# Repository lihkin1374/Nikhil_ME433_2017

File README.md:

Nikhil Marri
==============
March 28, 2017
----------------

My repository for ME 433: Advanced Mechatronics.

Spring quarter

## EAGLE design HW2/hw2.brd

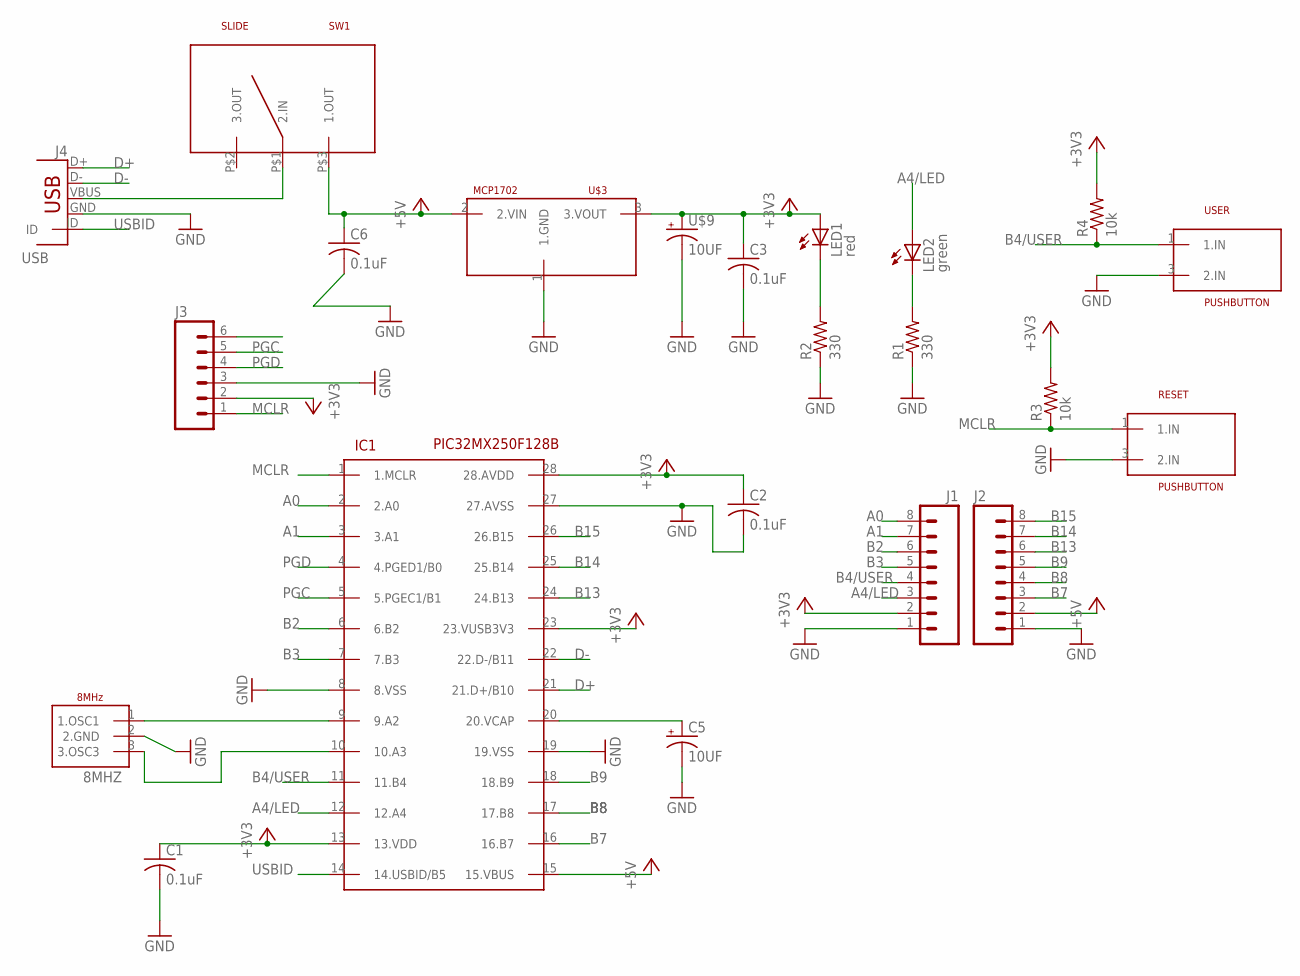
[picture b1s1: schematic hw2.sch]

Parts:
C1, C2, C3, C6: 0.1uF; C025-025X050
C5: 10UF; TT2D4
J1, J2: M08; 1X08_ROUND
J3: M06SILK_FEMALE_PTH; 1X06
J4: USB; USB-MB-H
LED1: red; LED3MM
LED2: green; LED3MM
PIC: PIC32MX250F128B; DIL28-3
R1, R2: 330; 0207/10
R3, R4: 10k; 0207/10
RESET: PUSHBUTTON; 1X03
SLIDE: SW1; SLIDEWITCH
U$2: 8MHZ; 1X03
U$3: MCP1702; TO92
U$9: 10UF; TT2D4
USER: PUSHBUTTON; 1X03

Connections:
+3V3: C1.1, C2.1, C3.1, J1.2, J3.2, LED1.A, PIC.13 (13.VDD), PIC.23 (23.VUSB3V3), PIC.28 (28.AVDD), R3.2, R4.2, U$3.3 (3.VOUT), U$9.+
+5V: C6.1, J2.2, PIC.15 (15.VBUS), SLIDE.P$3 (1.OUT), U$3.2 (2.VIN)
A0: J1.8, PIC.2 (2.A0)
A1: J1.7, PIC.3 (3.A1)
A4/LED: J1.3, LED2.A, PIC.12 (12.A4)
B2: J1.6, PIC.6 (6.B2)
B3: J1.5, PIC.7 (7.B3)
B4/USER: J1.4, PIC.11 (11.B4), R4.1, USER.1 (1.IN)
B7: J2.3, PIC.16 (16.B7)
B8: J2.4, PIC.17 (17.B8)
B9: J2.5, PIC.18 (18.B9)
B13: J2.6, PIC.24 (24.B13)
B14: J2.7, PIC.25 (25.B14)
B15: J2.8, PIC.26 (26.B15)
D+: J4.D+, PIC.21 (21.D+/B10)
D-: J4.D-, PIC.22 (22.D-/B11)
GND: C1.2, C2.2, C3.2, C5.-, C6.2, J1.1, J2.1, J3.3, J4.GND, PIC.8 (8.VSS), PIC.19 (19.VSS), PIC.27 (27.AVSS), R1.1, R2.1, RESET.3 (2.IN), U$2.2 (2.GND), U$3.1 (1.GND), U$9.-, USER.3 (2.IN)
MCLR: J3.1, PIC.1 (1.MCLR), R3.1, RESET.1 (1.IN)
unnamed: LED2.K (C), R1.2
unnamed: J4.VBUS, SLIDE.P$1 (2.IN)
unnamed: LED1.K (C), R2.2
unnamed: PIC.9 (9.A2), U$2.1 (1.OSC1)
unnamed: PIC.10 (10.A3), U$2.3 (3.OSC3)
unnamed: C5.+, PIC.20 (20.VCAP)
PGC: J3.5, PIC.5 (5.PGEC1/B1)
PGD: J3.4, PIC.4 (4.PGED1/B0)
USBID: J4.ID, PIC.14 (14.USBID/B5)

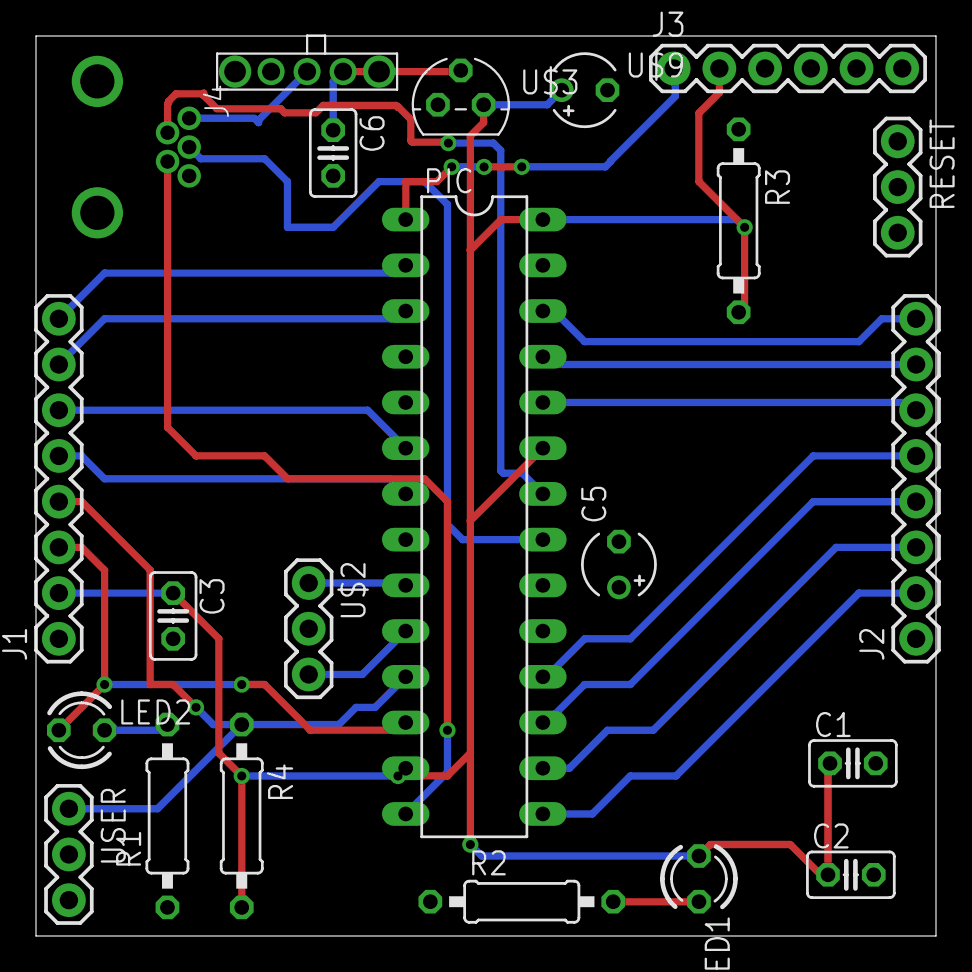
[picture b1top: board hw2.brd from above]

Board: 2 copper layers, 50.0 x 50.0 mm, 22 parts (0 on the bottom side), 27 nets.

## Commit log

2017-03-28 :confetti_ball: Added .gitattributes & .gitignore files
2017-03-28 My first commit!
2017-03-28 just syncing
2017-03-28 circuit diag
2017-03-29 oscillations in scope
2017-03-29 no oscillations after adding both capacitors
2017-03-29 clean 3.3 V after adding both capacitors
2017-03-30 full circuit
2017-03-30 main started
2017-03-30 main code
2017-04-01 2000Hz LED
2017-04-04 schematic
2017-04-05 library
2017-05-02 corrected code
    HW1 done
2017-05-02 spi wiring
    DAC_schematic
2017-05-02 code
    Main + Library
2017-05-03 code changed
    working now
2017-05-03 waves
2017-05-03 circuit diag added
    i2c circuit
2017-05-03 main code
    main added
2017-05-03 header file
    header code added
2017-05-03 i2c library
    i2c library added
2017-05-06 HW6 started
2017-05-06 header file
2017-05-06 ILI9163C
2017-05-06 made changes to main
2017-05-08 started HW7
2017-05-08 LCD header
2017-05-08 LCD library
2017-05-08 I2C master
2017-05-08 I2C header
2017-05-09 finished HW7
2017-05-11 finished HW8
2017-05-13 started HW9
2017-05-13 working on the code
2017-05-14 started HW10
2017-05-14 finished C code
2017-05-14 still working on HW9
2017-05-15 finished HW9
2017-05-16 working on HW10
2017-05-16 filtered z accelarations
2017-05-16 HW10 done
2017-05-17 started HW11
2017-05-17 IMU mouse controller
2017-05-18 finished HW12
2017-05-19 HW13 done green lines
2017-05-20 started HW14
2017-05-20 modified harmony USB code
2017-05-21 edited app.c code
2017-05-21 added IMU code
2017-05-21 added mouse control code
2017-05-26 gerber files
2017-05-26 full PCB files
2017-05-26 full PCB gerber files
2017-05-27 made changes to the PIC code
2017-05-28 working on androidUSB code
2017-05-28 designed part1
2017-05-29 working on androidPIC
2017-05-30 finished HW14
2017-06-07 designed the box
2017-06-07 designed the living hinge side
2017-06-07 added wheel design
2017-06-07 3d printed the wheel
2017-06-07 assembled the box
2017-06-08 working on the pic code
2017-06-08 testing the motor code
2017-06-08 motor code partly done
2017-06-09 added screenshot of the app
2017-06-10 completed motor control
2017-06-10 uploaded android code
